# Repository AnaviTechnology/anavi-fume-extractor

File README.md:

# ANAVI Fume Extractor

ANAVI Fume Extractor is an open source hardware development board with ESP8266 and connector for 5V USB-powered fan for absorbing smoke. It features:

* ESP8266 WiFi microcontroller
* Connector for 5V DC fan
* Dedicated slot for I2C OLED display
* Slots for up to 3 plug and play I2C sensors for temperature, barometric pressure, humidity and light
* Slot for analog MQ gas sensor
* UART (Universal asynchronous receiver/transmitter) pins for debugging

[Open source software for ANAVI Fume Extractor written as an Arduino sketch is also available at GitHub](https://github.com/AnaviTechnology/anavi-fume-extractor-sw).

# License

The project is released under the [Creative Commons Attribution-ShareAlike 4.0 International (CC BY-SA 4.0)](https://creativecommons.org/licenses/by-sa/4.0/).

Note: This is a human-readable summary of (and not a substitute for) the [license](https://creativecommons.org/licenses/by-sa/4.0/legalcode).

You are free to:

Share — copy and redistribute the material in any medium or format Adapt — remix, transform, and build upon the material for any purpose, even commercially. The licensor cannot revoke these freedoms as long as you follow the license terms. Under the following terms:

Attribution — You must give appropriate credit, provide a link to the license, and indicate if changes were made. You may do so in any reasonable manner, but not in any way that suggests the licensor endorses you or your use. ShareAlike — If you remix, transform, or build upon the material, you must distribute your contributions under the same license as the original. No additional restrictions — You may not apply legal terms or technological measures that legally restrict others from doing anything the license permits. Notices:

You do not have to comply with the license for elements of the material in the public domain or where your use is permitted by an applicable exception or limitation. No warranties are given. The license may not give you all of the permissions necessary for your intended use. For example, other rights such as publicity, privacy, or moral rights may limit how you use the material.

You will have to provide a link to the original creator of the project http://www.anavi.technology on any documentation or website.

Credit can be attributed through a link to the creator website: http://www.anavi.technology

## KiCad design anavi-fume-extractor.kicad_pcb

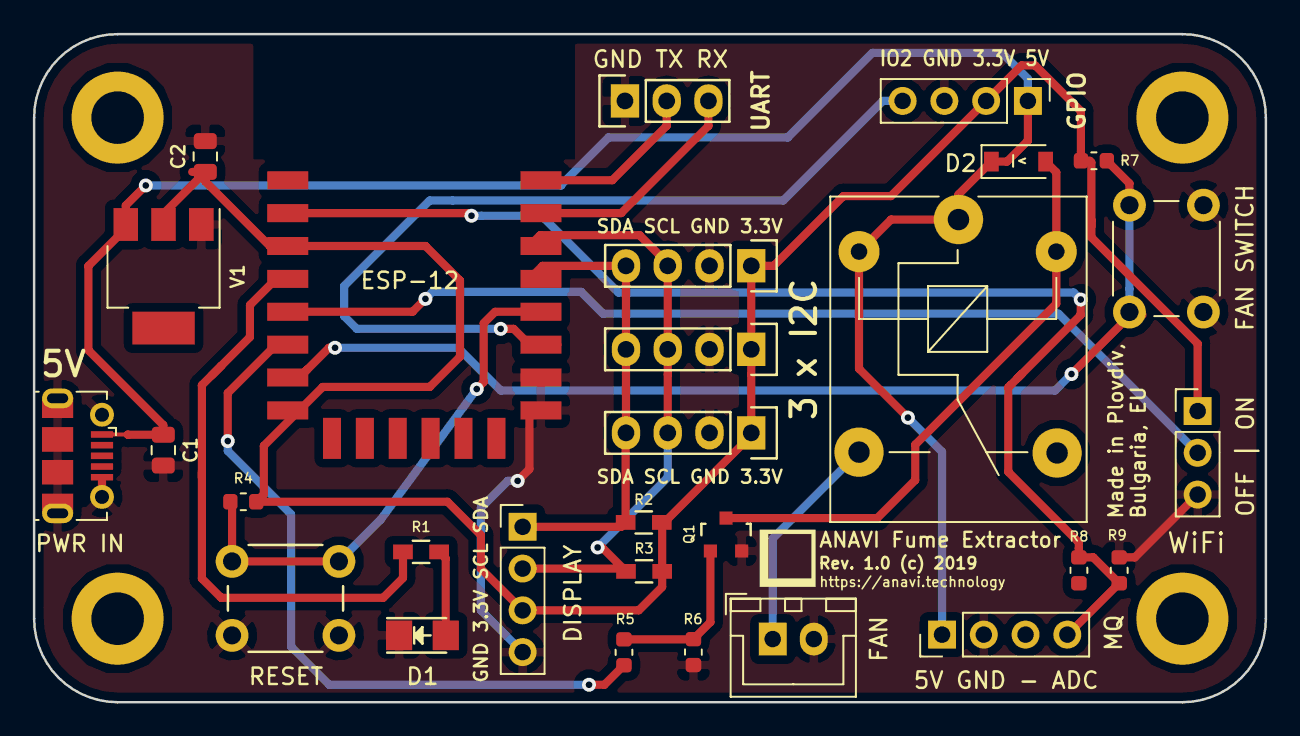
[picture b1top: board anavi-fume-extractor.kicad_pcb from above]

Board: 2 copper layers, 74.9 x 40.6 mm, 29 parts (0 on the bottom side), 18 nets.

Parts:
C1, C2: 10uF; C_0805_2012Metric
D1: LED; LED_1206
D2: 1N4148W; D_SOD-123
DISPLAY: Conn_01x04; PinHeader_1x04_P2.54mm_Vertical
ESP-12: ESP-12E; ESP-12E_SMD
FAN: Conn_01x02; JST_XH_B02B-XH-A_1x02_P2.50mm_Vertical
FAN SWITCH: SW_DIP_x01; SW_PUSH_6mm_h4.3mm
GPIO: Conn_01x04; PinHeader_1x04_P2.54mm_Vertical
K1: SANYOU_SRD_Form_C; Relay_SPDT_SANYOU_SRD_Series_Form_C
MQ: Conn_01x04; PinHeader_1x04_P2.54mm_Vertical
P1: CONN_01X03; Pin_Header_Straight_1x03
PWR IN: USB_B_Micro; USB_Micro-B_Molex-105017-0001
Q1: BC817; SOT-23
R1: 68R; R_0603_HandSoldering
R2, R3: 4,7K; R_0603_HandSoldering
R4, R7: 2K; R_0603_1608Metric
R5: 2,7K; R_0603_1608Metric
R6: 27K; R_0603_1608Metric
R8: 220K; R_0603_1608Metric
R9: 56K; R_0603_1608Metric
RESET: SW_DIP_x01; SW_PUSH_6mm_h4.3mm
U1, U2, U3: I2C_SENS_1; Pin_Header_Straight_1x04
V1: LD1117S33TR; SOT-223
WiFi: ConfigWiFi; PinHeader_1x03_P2.54mm_Vertical

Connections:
+3V3: C2.1, DISPLAY.3, ESP-12.3, ESP-12.8, GPIO.2, R2.1, R3.1, R4.2, R7.1, U1.1, U2.1, U3.1, V1.2, WiFi.1
+5V: C1.1, D2.1, GPIO.1, K1.1, K1.2, MQ.1, PWR IN.1, V1.3
GND: C1.2, C2.2, D1.1, DISPLAY.4, ESP-12.9, ESP-12.10, FAN.2, FAN SWITCH.1, GPIO.3, MQ.2, P1.1, PWR IN.5, PWR IN.6, Q1.2, R6.2, R9.2, RESET.1, U1.2, U2.2, U3.2, V1.1, WiFi.3
unnamed: D1.2, R1.2
unnamed: D2.2, K1.5, Q1.3
unnamed: ESP-12.2, MQ.4, R8.2, R9.1
unnamed: ESP-12.4, R1.1
unnamed: ESP-12.5, WiFi.2
unnamed: ESP-12.6, R5.1
unnamed: ESP-12.7, FAN SWITCH.2, R7.2
unnamed: ESP-12.11, GPIO.4
unnamed: ESP-12.12, R4.1, RESET.2
unnamed: DISPLAY.1, ESP-12.13, R2.2, U1.4, U2.4, U3.4
unnamed: DISPLAY.2, ESP-12.14, R3.2, U1.3, U2.3, U3.3
unnamed: ESP-12.15, P1.3
unnamed: ESP-12.16, P1.2
unnamed: FAN.1, K1.3
unnamed: Q1.1, R5.2, R6.1

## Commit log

2019-07-14 anavi-fume-extractor.kicad_pcb: Move capacitor
    Move capacitor C1 to be closer to the microUSB connector.
    Suggested-by: Rangel Ivanov <rangelivanov88@gmail.com>
2019-09-16 anavi-fume-extractor.kicad_pcb: Assembly notes
    Add notes to simplify the assembly of the board.
2019-11-16 README.md: Fix link
    Fix the link to the open source software.

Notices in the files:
anavi-fume-extractor.kicad_pcb:
Rev. 1.0 (c) 2019
